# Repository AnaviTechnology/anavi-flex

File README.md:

# ANAVI Flex Raspberry Pi HAT

ANAVI Flex is an open source hardware Raspberry Pi HAT (add-on board) for rapid prototyping of Internet of Things (IoT) powered by free and open source software. It features:

* IR transmitter (IR LED)
* IR receiver (IR photo sensor)
* Relay
* Piezoelectric speaker (buzzer)
* Button
* RGB LED
* Slot for modular 16x2 LCD character display
* Slots for up to 5 plug and play I2C sensors for temperature, barometric pressure, humidity and light
* UART (Universal asynchronous receiver/transmitter) pins for debugging

The project was brought to life through a [crowdfunding campaign in IndieGoGo](https://igg.me/at/Rzjuluvxe6Y/10833949). You can still order it at [Tindie](https://www.tindie.com/products/anavi/anavi-flex-raspberry-pi-hat-for-iot/).

# Story

ANAVI Flex started as a small hobby project by Leon Anavi in November 2015. Initially the project was using off the shelf components but soon after that Leon decided to create his own Raspberry Pi HAT for easy IoT prototyping.

Inspired by Olimex and Tsvetan Uzunov's presentations about open source hardware at FOSDEM and Hackaday Belgrade, Leon insisted on using the free and open source electronics design automation suite KiCAD for the PCB design. In April 2016, the software engineer Leon bought his first soldering iron from Olimex and started working on the first hardware prototypes.

Designing PCB requires a lot of hardware skills and experience so Leon needed help. It was not easy to find a suitable hardware engineer familiar with KiCAD. After making a lot of contacts and speaking to various engineers finally Leon found the right people. Thanks to the PCB manufacturing services of OSH Park the first PCB prototypes were ready at the end of June 2016.

As expected the first version was far from perfect. There were  a few bugs which were quickly fixed. The next hardware revision and a small-run batch was ready in August 2016. It featured a new buzzer, a new button and a potentiometer for controlling the light and contrast of the LCD display module. 

In September 2016, after a lot of hard work, the first version of the user's manual of ANAVI Flex was released with open source examples written in Python and the C programming language.

In October 2016 first prototypes of ANAVI Flex were shipped to developers and bloggers. Another hardware revision with minor improvements was made and a small quantity of ANAVI Flex Raspberry Pi HATs was released on sale and quickly went out of stock in Tindie.

On 1 November 2016 ANAVI Flex crowdfunding campaign was launched in IndieGoGo. In 2017 the project was renamed from RabbitMax to ANAVI. The crowdfunding campaing was successful and all perks were shipped on time. Now can still order ANAVI Flex HAT at [Tindie](https://www.tindie.com/products/anavi/anavi-flex-raspberry-pi-hat-for-iot/).

# License

The project is released under the [Creative Commons Attribution-ShareAlike 4.0 International (CC BY-SA 4.0)](https://creativecommons.org/licenses/by-sa/4.0/).

Note: This is a human-readable summary of (and not a substitute for) the [license](https://creativecommons.org/licenses/by-sa/4.0/legalcode).

You are free to:

Share — copy and redistribute the material in any medium or format Adapt — remix, transform, and build upon the material for any purpose, even commercially. The licensor cannot revoke these freedoms as long as you follow the license terms. Under the following terms:

Attribution — You must give appropriate credit, provide a link to the license, and indicate if changes were made. You may do so in any reasonable manner, but not in any way that suggests the licensor endorses you or your use. ShareAlike — If you remix, transform, or build upon the material, you must distribute your contributions under the same license as the original. No additional restrictions — You may not apply legal terms or technological measures that legally restrict others from doing anything the license permits. Notices:

You do not have to comply with the license for elements of the material in the public domain or where your use is permitted by an applicable exception or limitation. No warranties are given. The license may not give you all of the permissions necessary for your intended use. For example, other rights such as publicity, privacy, or moral rights may limit how you use the material.

You will have to provide a link to the original creator of the project http://www.anavi.technology on any documentation or website.

Credit can be attributed through a link to the creator website: http://www.anavi.technology

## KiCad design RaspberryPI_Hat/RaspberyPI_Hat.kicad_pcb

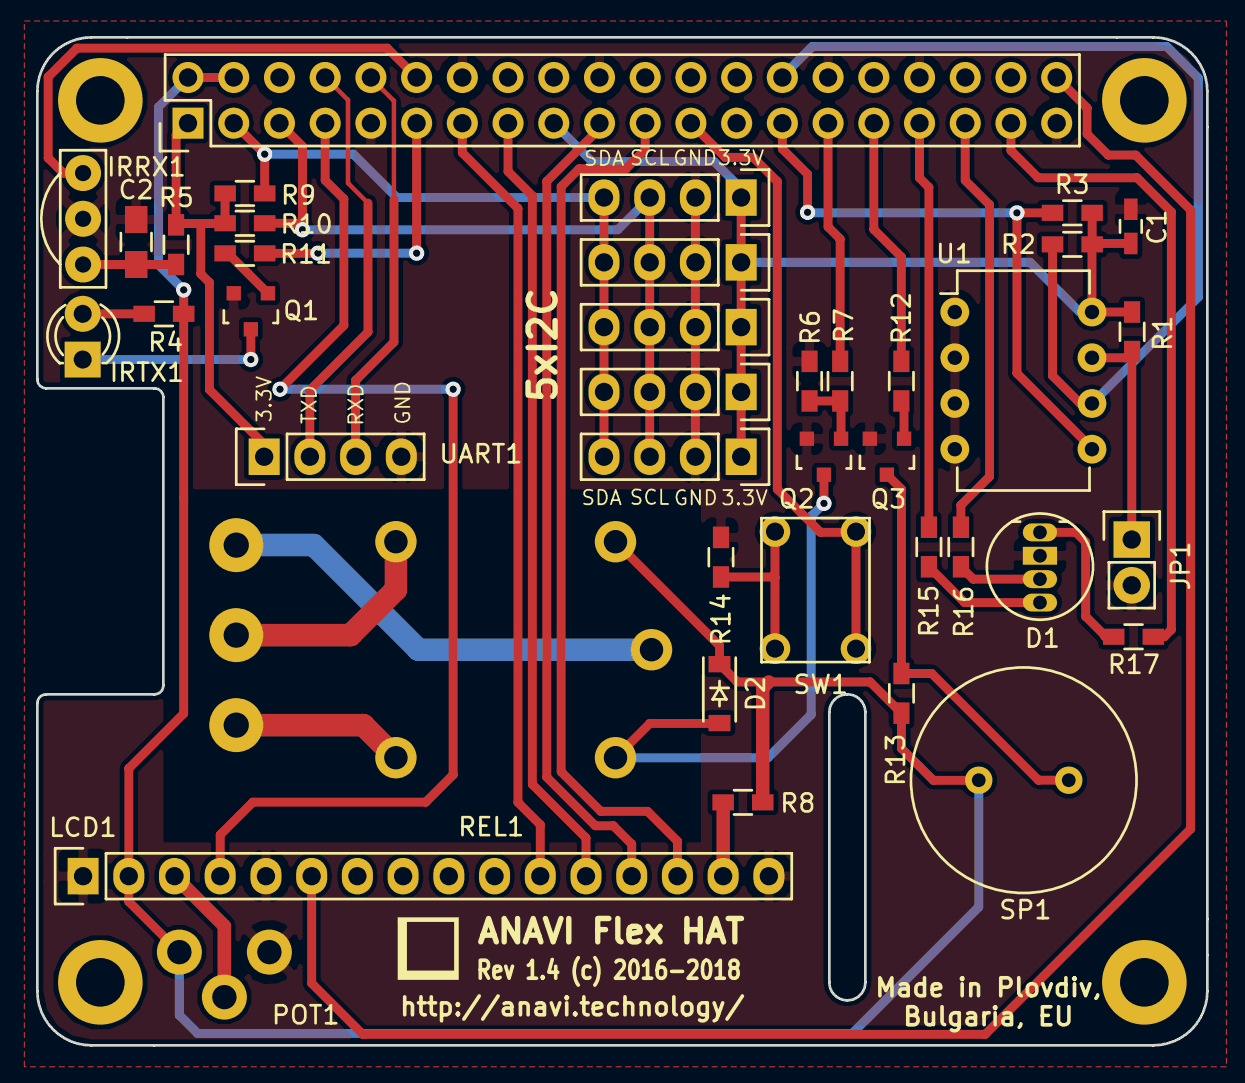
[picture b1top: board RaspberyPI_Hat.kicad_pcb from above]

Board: 2 copper layers, 65.0 x 56.0 mm, 45 parts (0 on the bottom side), 41 nets.

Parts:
C1: 0.1; C_0603_HandSoldering
C2: 4.7; C_0805_HandSoldering
D1: LED_RCBG; LED-RGB-5MM_Common_Anode
D2: 1N4148; SOD-123
IRRX1: TSOP34838; TSOP38X
IRTX1: L-934F3BT; LED-3MM
JP1: JUMPER; Pin_Header_Straight_1x02
KL1: CONN_01X03; KLEMA_1x3
LCD1: LCD_16x2; Pin_Header_Straight_1x16
POT1: 10K; POT_VERT
Q1, Q2, Q3: BC817; SOT-23
R1, R13, R14: 1K; R_0603_HandSoldering
R2, R3, R9, R10: 4.7K; R_0603_HandSoldering
R4: 380; R_0603_HandSoldering
R5: 470; R_0603_HandSoldering
R6: 27K; R_0603_HandSoldering
R7: 2.7K; R_0603_HandSoldering
R8: 330; R_0603_HandSoldering
R11, R12: 10K; R_0603_HandSoldering
R15, R17: 60; R_0603_HandSoldering
R16: 300; R_0603_HandSoldering
RASP_CONN1: Raspberry_PI; Pin_Header_Straight_2x20
REF1, REF2, REF3, REF4: MountingHole_2.7mm_M2.5_DIN965_Pad
REL1: RAS-05-15
SENS1, SENS2, SENS3, SENS4, SENS5: I2C_SENS_1; Pin_Header_Straight_1x04
SP1: MCKPI-G1410-3668; MURATA_PKM13
SW1: SW_PUSH; TACT_SW_6
U1: CAT24C32WI-GT3; DIP-8_W7.62mm
UART1: CONN_01X04; Pin_Header_Straight_1x04

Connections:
+3V3: C1.1, R1.1, R2.1, R3.1, R5.1, R9.1, R10.1, RASP_CONN1.1, RASP_CONN1.17, SENS1.1, SENS2.1, SENS3.1, SENS4.1, SENS5.1, U1.8, UART1.1
+5V: D2.1, LCD1.2, POT1.1, R4.1, R8.2, R13.1, RASP_CONN1.2, RASP_CONN1.4, REL1.2, SP1.1
/D4: LCD1.11, RASP_CONN1.13
/D5: LCD1.12, RASP_CONN1.15
/D6: LCD1.13, RASP_CONN1.19
/D7: LCD1.14, RASP_CONN1.21
/EN: LCD1.6, RASP_CONN1.40
/LED1: R16.1, RASP_CONN1.35
/LED2: R15.1, RASP_CONN1.33
/LED3: R17.2, RASP_CONN1.37
/RS: LCD1.4, RASP_CONN1.7
/RXD: RASP_CONN1.10, UART1.3
/TXD: RASP_CONN1.8, UART1.2
GND: C1.2, C2.2, D1.2, IRRX1.2, JP1.2, LCD1.1, LCD1.5, LCD1.16, POT1.3, Q1.2, Q2.2, Q3.2, R6.1, R14.2, RASP_CONN1.6, RASP_CONN1.9, RASP_CONN1.14, RASP_CONN1.20, RASP_CONN1.25, RASP_CONN1.30, RASP_CONN1.34, RASP_CONN1.39, SENS1.2, SENS2.2, SENS3.2, SENS4.2, SENS5.2, U1.1, U1.2, U1.3, U1.4, UART1.4
unnamed: C2.1, IRRX1.3, R5.2
unnamed: D1.1, R17.1
unnamed: D1.3, R16.2
unnamed: D1.4, R15.2
unnamed: D2.2, Q2.3, REL1.4
unnamed: IRRX1.1, RASP_CONN1.12
unnamed: IRTX1.1, Q1.3
unnamed: IRTX1.2, R4.2
unnamed: JP1.1, R1.2, U1.7
unnamed: KL1.1, REL1.5
unnamed: KL1.2, REL1.1
unnamed: KL1.3, REL1.3
unnamed: LCD1.3, POT1.2
unnamed: LCD1.15, R8.1
unnamed: Q1.1, R11.1
unnamed: Q2.1, R6.2, R7.1
unnamed: Q3.1, R12.1
unnamed: Q3.3, R13.2, SP1.2
unnamed: R2.2, RASP_CONN1.28, U1.6
unnamed: R3.2, RASP_CONN1.27, U1.5
unnamed: R7.2, RASP_CONN1.29
unnamed: R9.2, RASP_CONN1.3, SENS1.4, SENS2.4, SENS3.4, SENS4.4, SENS5.4
unnamed: R10.2, RASP_CONN1.5, SENS1.3, SENS2.3, SENS3.3, SENS4.3, SENS5.3
unnamed: R11.2, RASP_CONN1.11
unnamed: R12.2, RASP_CONN1.31
unnamed: R14.1, SW1.1
unnamed: RASP_CONN1.23, SW1.2

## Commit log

2016-03-30 Initial commit with contributors
2016-04-01 Първа версия с UEXT конектор
2016-04-01 Добавено реле
2016-04-01 Промяна на UEXT на 2x05 корпус
2016-04-01 Обърнат конектор 2x20
2016-04-04 Добавено LCD
2016-04-11 Добавени хедъри за сензори, бутон, зумер
2016-04-12 Добавен RG LED оправени корпуси
2016-04-12 no message
2016-04-12 mylibrary.lib added
2016-04-13 Започнато трасиране на платка
2016-04-15 Първи вариант PCB
2016-04-19 Rename mylibrary.lib_file to mylibrary.lib
2016-04-24 Рзместени IR и зумер, сменен RGB диод
2016-05-26 Last tweaks before first prototype run
2016-05-31 IR Diod moved to pin 11
2016-06-01 RS interface added
2016-06-03 Added logo
2016-06-04 Text on socket's pads
2016-06-04 Changed to 5 I2C sensors on headers
2016-06-04 scale_kicad_mod.py
2016-06-06 changed IRRT to pin 11 RS to pin 7
2016-06-06 changed common A to common Katode RGB LED
2016-06-06 Gerber and drill files added
2016-06-29 BOM added
2016-08-03 Moved relay and terminal, changed zummer, added trimmer for contrast control of LCD, added Made in Bulgaria, chnaged button, changed value of button resistor
2016-08-03 Changed trimmer part
2016-08-05 Add logo as png and svg
    Add files of the logo as svg and png.
2016-08-05 Change revision number
    Added separate footprint for rabbit logo
2016-08-05 Add rev 1.1 plots
2016-08-14 revision-1.0: Rename plots for v1.0
    Rename directory with plots according to the
    naming convension started by Rangel.
2016-08-14 RaspberyPI_Hat.kicad_pcb: Move and update labels
    The following changes have been applied to the
    silk screen:
    - Hide labels K and KL1
    - Move IRTX1
    - Move REL1
    - Move SW1
2016-08-16 Changed drill sizes for button and buzzer
2016-09-15 Buton drill holes sizes, buzzer, moved POT1
2016-10-15 POT1 connected to PIN3 of LCD, added R8, for LCD backlight current limit.
2016-10-27 RaspberyPI_Hat.kicad_pcb: Set version to 1.3
2016-11-01 README.md
    README added with general information, story and
    license details for RabbitMax Flex.
2016-11-05 RaspberyPI_Hat.kicad_pcb: rev 1.3
    Configure export options for revision 1.3
2016-12-28 F.Fab: SMT footprint assembly
    Add information about SMT footprint assembly.
2018-03-25 Update logo and change version to 1.4
    Change the logo and the text on the silkscreen.
2018-03-25 README.md: Update story
    Add details about the story of ANAVI Flex HAT.
2018-03-25 README.md: CC BY-SA 4.0
    Switch license to CC BY-SA 4.0 because my newer
    open source hardware projects are with it.

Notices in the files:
RaspberryPI_Hat/RaspberyPI_Hat.kicad_pcb:
Rev 1.4 (c) 2016-2018
